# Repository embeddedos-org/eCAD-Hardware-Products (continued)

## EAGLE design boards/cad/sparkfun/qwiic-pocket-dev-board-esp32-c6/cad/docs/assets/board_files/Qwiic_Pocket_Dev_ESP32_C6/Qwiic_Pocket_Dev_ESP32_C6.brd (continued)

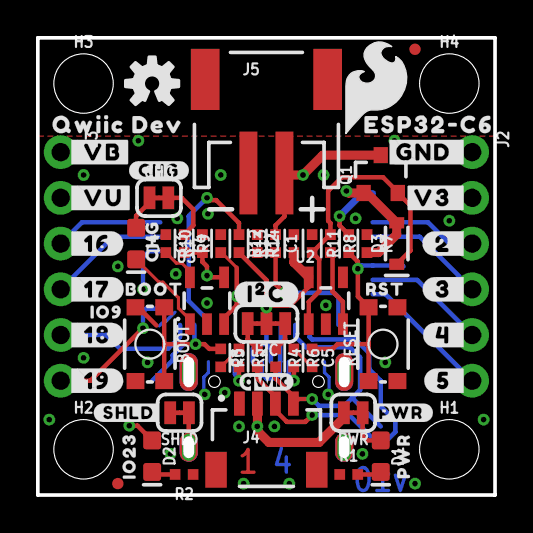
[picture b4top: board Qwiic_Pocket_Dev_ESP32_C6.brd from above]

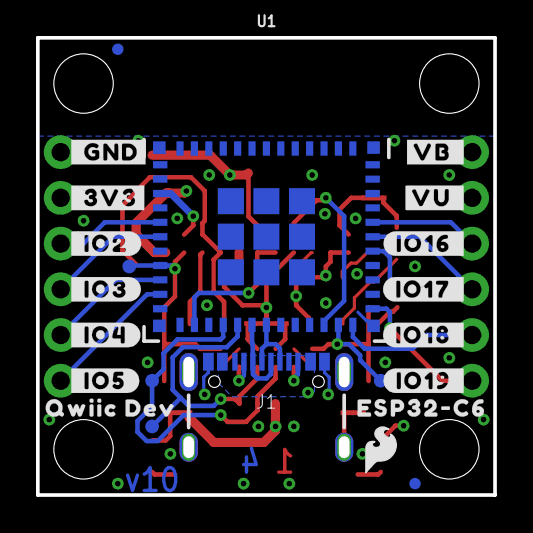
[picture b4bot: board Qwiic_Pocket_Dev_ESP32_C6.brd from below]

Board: 4 copper layers, 25.4 x 25.4 mm, 96 parts (23 on the bottom side), 35 nets.

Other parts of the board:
U$1: #_GND#0
U$2: #_3V3#0
U$3: #V3_#0
U$5: #GND_#0
U$6: SFE_LOGO_FLAME_.2
U$7: #VU_#0
U$8: #_VB#0
U$9, U$25: QWIIC_DEV0
U$10: SFE_LOGO_FLAME_.1
U$11, U$12: ESP32#C633
U$13: #_IO5#0
U$14: #_IO4#0
U$15: #_IO3#0
U$16: #_IO2#0
U$17: #IO16_#0
U$18: #IO17_#0
U$19: #IO18_#0
U$20: #IO19_#0
U$21: #5_#0
U$22: #4_#0
U$23: #I�C#0
U$24: ORDERING_INSTRUCTIONS
U$26: #PWR#0
U$27: #SHLD#0
U$28: IO230
U$30: PWR0
U$31: #CHG#0
U$32: CHG0
U$33: BOOT0
U$34: RST0
U$35: IO90
U$36: #VB_#0
U$37: #_VU#0
U$38: #3_#0
U$39: #2_#0
U$40: #_16#0
U$41: #_17#0
U$42: #_18#0
U$43: #_19#0

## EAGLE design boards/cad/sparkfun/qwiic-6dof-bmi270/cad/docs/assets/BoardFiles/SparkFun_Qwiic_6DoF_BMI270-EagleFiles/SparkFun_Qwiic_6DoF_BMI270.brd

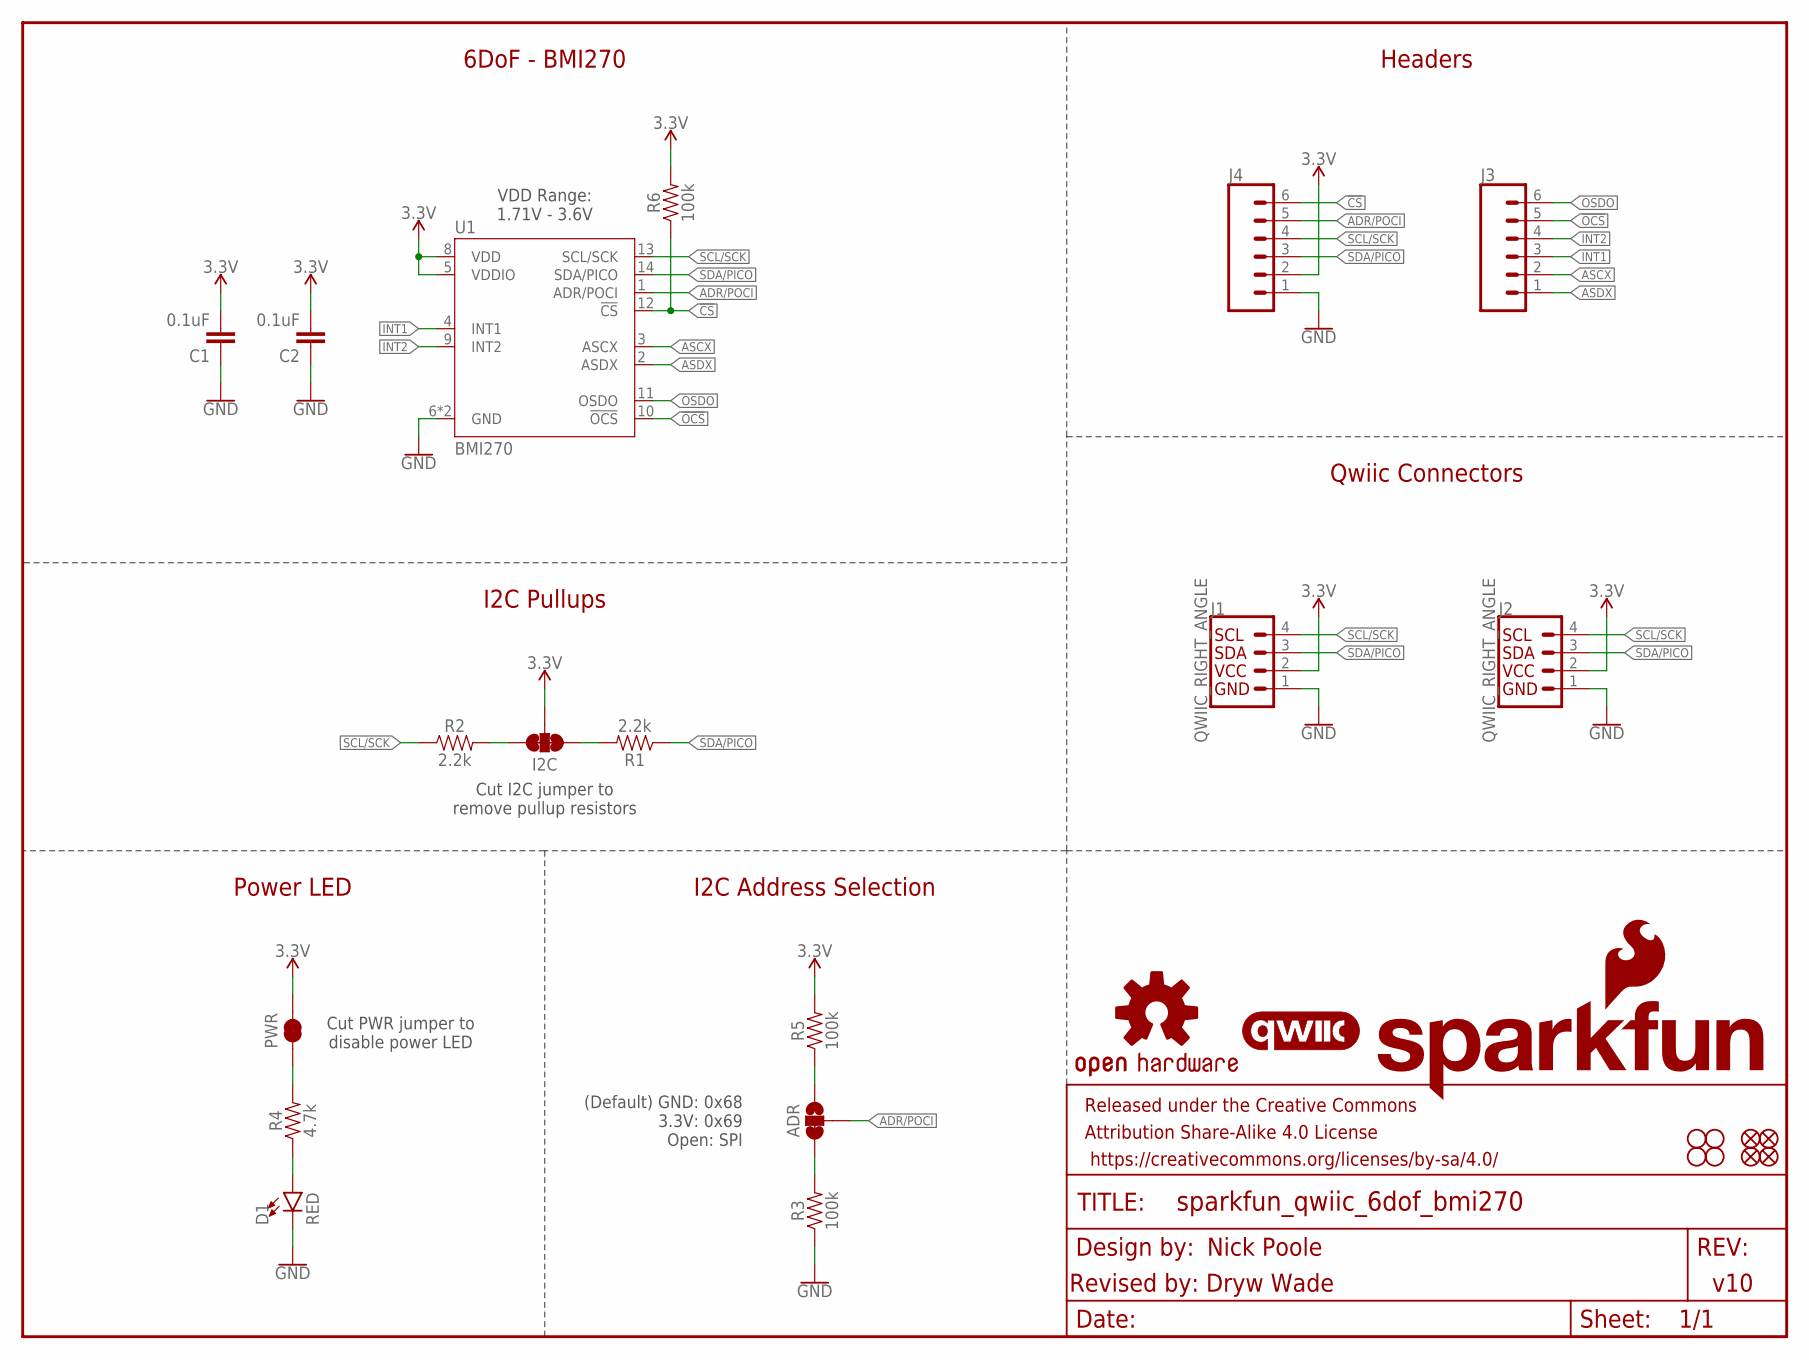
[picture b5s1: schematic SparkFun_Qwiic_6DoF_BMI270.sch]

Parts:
ADR: JUMPER-SMT_3_1-NC_TRACE_SILK; SMT-JUMPER_3_1-NC_TRACE_SILK
C1, C2: 0.1uF; 0603
D1: RED; LED-0603
FD1, FD2, FD3, FD4: FIDUCIAL1X2; FIDUCIAL-1X2
FRAME1: FRAME-LETTER; CREATIVE_COMMONS
H1, H2, H3, H4: STAND-OFF
I2C: JUMPER-SMT_3_2-NC_TRACE_SILK; SMT-JUMPER_3_2-NC_TRACE_SILK
J1, J2: QWIIC_RIGHT_ANGLE; JST04_1MM_RA
J3, J4: CONN_06NO_SILK_NO_POP; 1X06_NO_SILK
LOGO1: SFE_LOGO_NAME_FLAME.1_INCH; SFE_LOGO_NAME_FLAME_.1
LOGO2: QWIIC_LOGO_5MM; QWIIC_5MM
LOGO3: OSHW-LOGOS; OSHW-LOGO-S
PWR: JUMPER-SMT_2_NC_TRACE_SILK; SMT-JUMPER_2_NC_TRACE_SILK
R1, R2: 2.2k; 0603
R3, R5, R6: 100k; 0603
R4: 4.7k; 0603
U1: BMI270

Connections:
3.3V: C1.2, C2.2, I2C.2, J1.2, J2.2, J4.2, PWR.2, R5.2, R6.2, U1.5 (VDDIO), U1.8 (VDD)
!CS!: J4.6, R6.1, U1.12 (!CS!)
!OCS!: J3.5, U1.10 (!OCS!)
ADR/POCI: ADR.2, J4.5, U1.1 (ADR/POCI)
ASCX: J3.2, U1.3 (ASCX)
ASDX: J3.1, U1.2 (ASDX)
GND: C1.1, C2.1, D1.C, J1.1, J2.1, J4.1, R3.1, U1.6 (GND), U1.7 (GND)
INT1: J3.3, U1.4 (INT1)
INT2: J3.4, U1.9 (INT2)
unnamed: I2C.1, R1.2
unnamed: I2C.3, R2.2
unnamed: PWR.1, R4.2
unnamed: D1.A, R4.1
unnamed: ADR.1, R5.1
unnamed: ADR.3, R3.2
OSDO: J3.6, U1.11 (OSDO)
SCL/SCK: J1.4, J2.4, J4.4, R2.1, U1.13 (SCL/SCK)
SDA/PICO: J1.3, J2.3, J4.3, R1.1, U1.14 (SDA/PICO)

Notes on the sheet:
(Default) GND: 0x68 3.3V: 0x69 Open: SPI
Cut PWR jumper to disable power LED
Power LED
Headers
Qwiic Connectors
Nick Poole
Revised by: Dryw Wade
v10
6DoF - BMI270
Cut I2C jumper to remove pullup resistors
VDD Range: 1.71V - 3.6V
I2C Address Selection
I2C Pullups

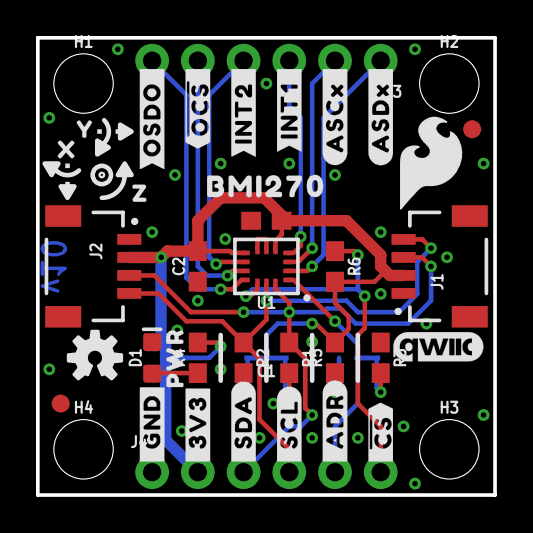
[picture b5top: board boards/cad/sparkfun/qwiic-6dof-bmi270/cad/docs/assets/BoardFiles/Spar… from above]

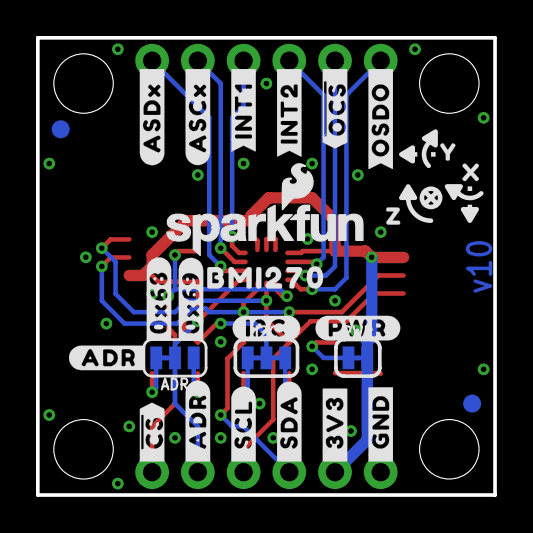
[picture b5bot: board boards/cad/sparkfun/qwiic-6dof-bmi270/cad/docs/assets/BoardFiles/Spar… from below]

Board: 2 copper layers, 25.4 x 25.4 mm, 69 parts (27 on the bottom side), 18 nets.

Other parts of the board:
U$1: #I2C#0
U$2, U$14: #_SDA#0
U$3: SFE_LOGO_FLAME_.2
U$4: #PWR#0
U$5: #ADR#0
U$6: #0X68#0
U$7, U$13: #_3V3#0
U$8, U$17: #_#CS##0
U$9, U$16: #_ADR#0
U$10, U$15: #_SCL#0
U$11, U$27: #ASDX_#0
U$12, U$19: #_GND#0
U$18: #0X69#0
U$20, U$21: BMI2700
U$22, U$28: #ASCX_#0
U$23, U$29: #INT1_#0
U$24, U$30: #INT2_#0
U$25, U$31: ##OCS#_#0
U$26, U$32: #OSDO_#0
U$33: ORDERING_INSTRUCTIONS
U$34: PWR0
U$79, U$88: X0
U$80, U$89: Y0
U$81, U$90: Z0

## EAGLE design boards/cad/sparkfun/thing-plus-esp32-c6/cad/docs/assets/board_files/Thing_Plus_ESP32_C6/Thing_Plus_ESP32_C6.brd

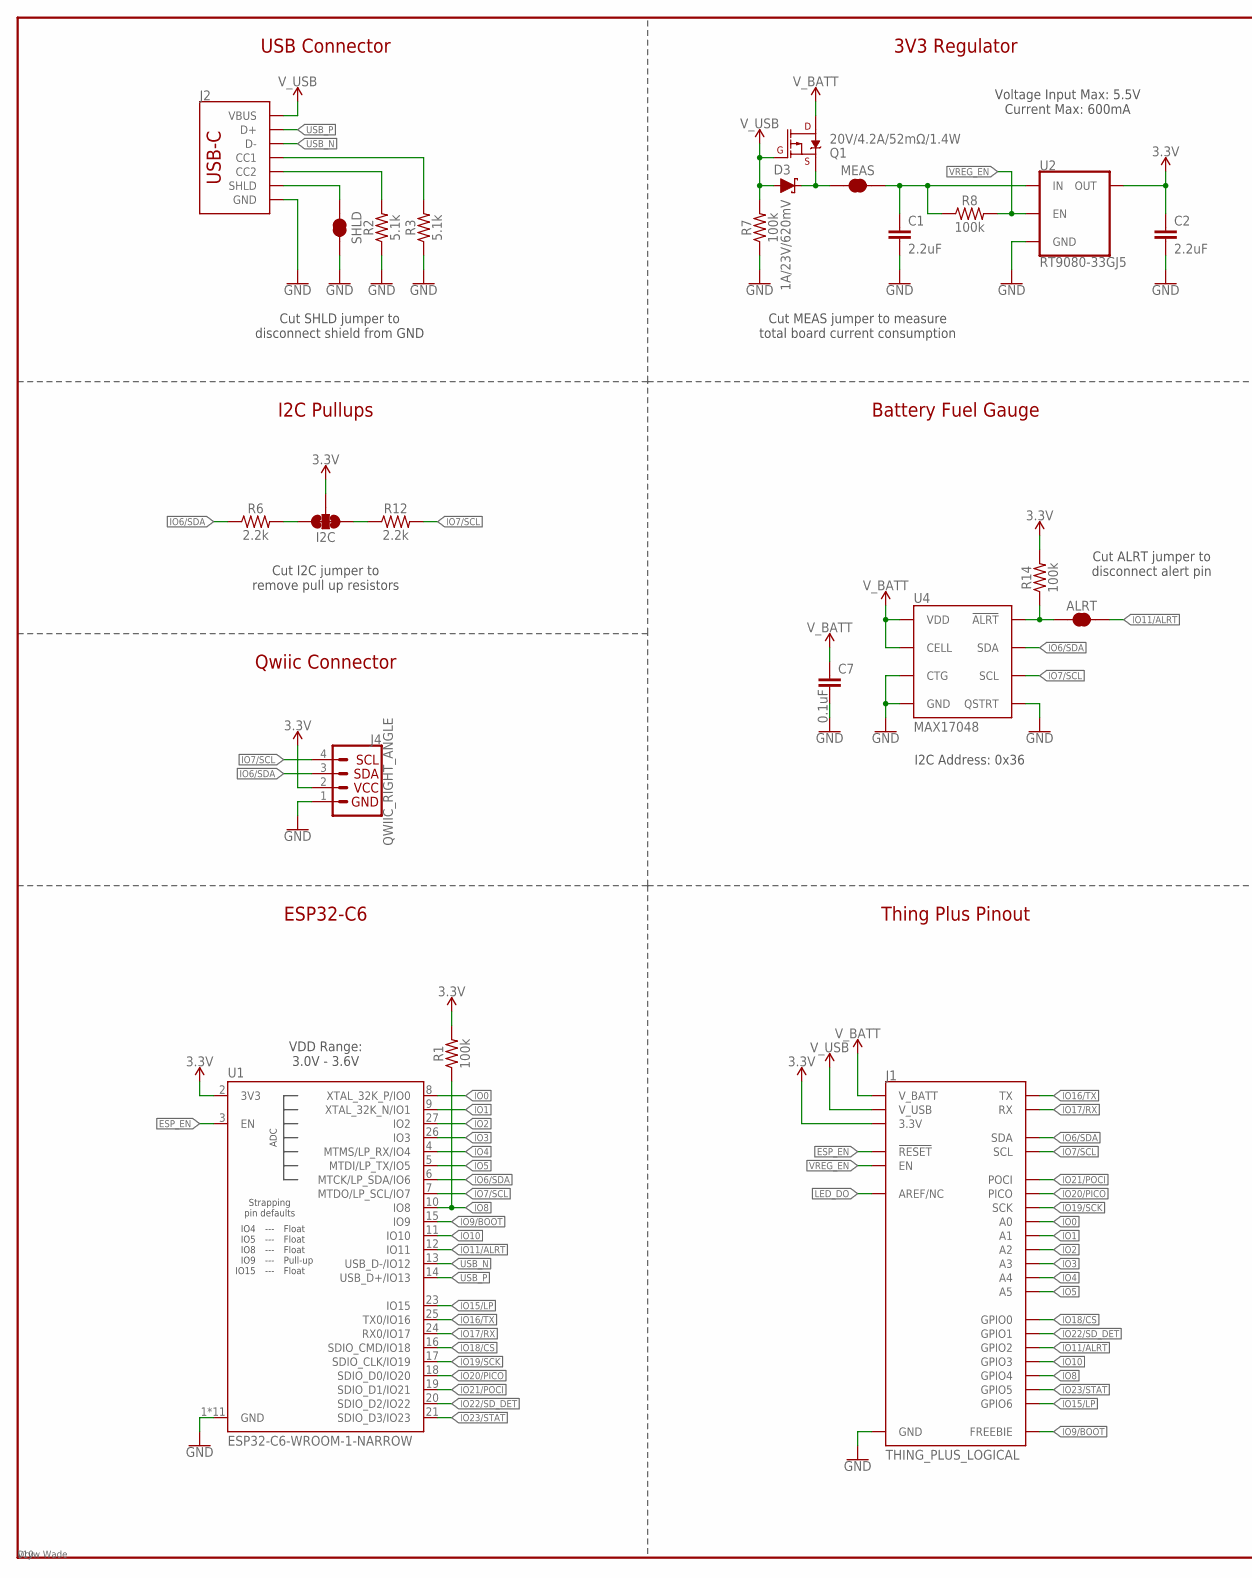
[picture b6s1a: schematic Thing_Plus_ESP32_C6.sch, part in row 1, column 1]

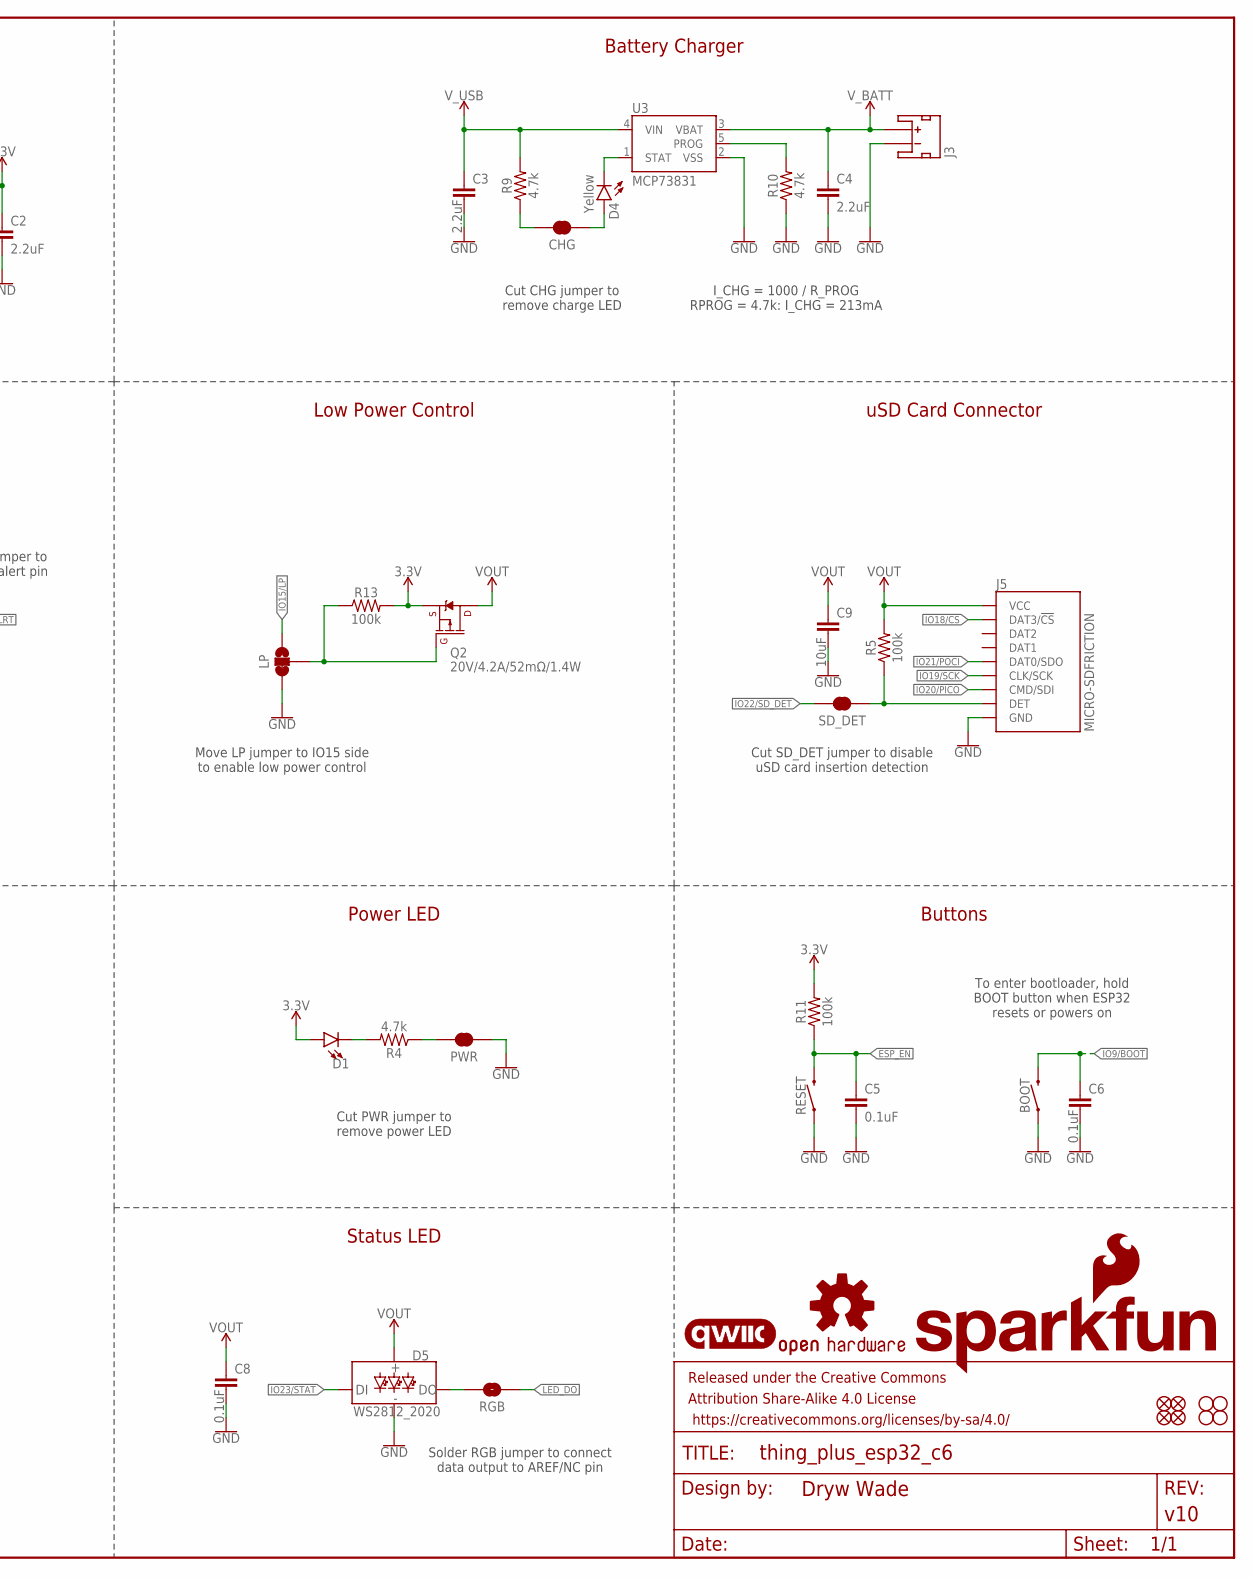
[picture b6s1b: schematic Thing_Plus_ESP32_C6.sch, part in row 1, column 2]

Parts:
ALRT: JUMPER-SMT_2_NC_TRACE_SILK; SMT-JUMPER_2_NC_TRACE_SILK
BOOT: MOMENTARY-SWITCH-SPST-SMD-4.6X2.8MM; TACTILE_SWITCH_SMD_4.6X2.8MM
C1, C2, C3, C4: 2.2uF; 0603
C5, C6, C7, C8: 0.1uF; 0603
C9: 10uF; 0603
CHG: JUMPER-SMT_2_NC_TRACE_SILK; SMT-JUMPER_2_NC_TRACE_SILK
D1: LED-RED_0603-KB; LED-0603
D3: 1A/23V/620mV; SOD-323
D4: Yellow; LED-0603
D5: WS2812_2020; WS2812-2020
FD1, FD2, FD3, FD4: FIDUCIALUFIDUCIAL; FIDUCIAL-MICRO
FRAME1: FRAME-LEDGER; CREATIVE_COMMONS
H1, H2, H3, H4: STAND-OFF
I2C: JUMPER-SMT_3_2-NC_TRACE_SILK; SMT-JUMPER_3_2-NC_TRACE_SILK
J1: THING_PLUS_LOGICAL; THING_PLUS
J2: USB_C_4-LAYER_PADS; USB-C-16P_4LAYER-PADS
J3: JST_2MM_MALE; JST-2-SMD
J4: QWIIC_RIGHT_ANGLE; JST04_1MM_RA
J5: MICRO-SDFRICTION; MICROSD_TINY
LOGO1: SFE_LOGO_NAME_FLAME.1_INCH; SFE_LOGO_NAME_FLAME_.1
LOGO2: QWIIC_LOGO_4MM; QWIIC_4MM
LOGO3: OSHW-LOGOM; OSHW-LOGO-M
LP: JUMPER-SMT_3_1-NC_TRACE_SILK; SMT-JUMPER_3_1-NC_TRACE_SILK
MEAS: JUMPER-COMBO_2_NC_TRACE; COMBO-JUMPER_2_NC_TRACE
PWR: JUMPER-SMT_2_NC_TRACE_SILK; SMT-JUMPER_2_NC_TRACE_SILK
Q1, Q2: 20V/4.2A/52mΩ/1.4W; SOT23-3
R1, R5, R7, R8, R11, R13, R14: 100k; 0603
R2, R3: 5.1k; 0603
R4, R9, R10: 4.7k; 0603
R6, R12: 2.2k; 0603
RESET: MOMENTARY-SWITCH-SPST-SMD-4.6X2.8MM; TACTILE_SWITCH_SMD_4.6X2.8MM
RGB: JUMPER-SMT_2_NO_SILK; SMT-JUMPER_2_NO_SILK
SD_DET: JUMPER-SMT_2_NC_TRACE_SILK; SMT-JUMPER_2_NC_TRACE_SILK
SHLD: JUMPER-SMT_2_NC_TRACE_SILK; SMT-JUMPER_2_NC_TRACE_SILK
U1: ESP32-C6-WROOM-1-NARROW
U2: RT9080-33GJ5; SOT23-5
U3: MCP73831; SOT23-5
U4: MAX17048; DFN-8

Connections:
3.3V: C2.1, D1.A, I2C.2, J1.27 (3.3V), J4.2, Q2.2 (S), R1.2, R11.2, R13.2, R14.2, U1.2 (3V3), U2.5 (OUT)
ESP_EN: C5.1, J1.28 (!RESET), R11.1, RESET.3 (2), RESET.4 (2), U1.3 (EN)
GND: BOOT.1, BOOT.2 (1), C1.2, C2.2, C3.2, C4.2, C5.2, C6.2, C7.2, C8.2, C9.2, D5.GND, J1.25 (GND), J2.GND, J2.GND2 (GND), J3.1 (-), J4.1, J5.6 (GND), J5.GND1 (GND), J5.GND2 (GND), J5.GND3 (GND), J5.GND4 (GND), J5.GND5 (GND), J5.GND6 (GND), LP.3, PWR.1, R2.1, R3.1, R7.1, R10.1, RESET.1, RESET.2 (1), SHLD.2, U1.1 (GND), U1.28 (GND), U1.29 (GND), U1.30 (GND), U1.31 (GND), U1.32 (GND), U1.33 (GND), U1.34 (GND), U1.35 (GND), U1.36 (GND), U1.37 (GND), U2.2 (GND), U3.2 (VSS), U4.1 (CTG), U4.4 (GND), U4.6 (QSTRT), U4.9 (GND)
IO0: J1.24 (A0), U1.8 (XTAL_32K_P/IO0)
IO1: J1.23 (A1), U1.9 (XTAL_32K_N/IO1)
IO2: J1.22 (A2), U1.27 (IO2)
IO3: J1.21 (A3), U1.26 (IO3)
IO4: J1.20 (A4), U1.4 (MTMS/LP_RX/IO4)
IO5: J1.19 (A5), U1.5 (MTDI/LP_TX/IO5)
IO6/SDA: J1.1 (SDA), J4.3, R6.1, U1.6 (MTCK/LP_SDA/IO6), U4.8 (SDA)
IO7/SCL: J1.2 (SCL), J4.4, R12.2, U1.7 (MTDO/LP_SCL/IO7), U4.7 (SCL)
IO8: J1.5 (GPIO4), R1.1, U1.10 (IO8)
IO9/BOOT: BOOT.3 (2), BOOT.4 (2), C6.1, J1.13 (FREEBIE), U1.15 (IO9)
IO10: J1.6 (GPIO3), U1.11 (IO10)
IO11/!ALRT!: ALRT.2, J1.7 (GPIO2), U1.12 (IO11)
IO15/LP: J1.3 (GPIO6), LP.1, U1.23 (IO15)
IO16/TX: J1.14 (TX), U1.25 (TX0/IO16)
IO17/RX: J1.15 (RX), U1.24 (RX0/IO17)
IO18/!CS!: J1.9 (GPIO0), J5.2 (DAT3/!CS!), U1.16 (SDIO_CMD/IO18)
IO19/SCK: J1.18 (SCK), J5.5 (CLK/SCK), U1.17 (SDIO_CLK/IO19)
IO20/PICO: J1.17 (PICO), J5.3 (CMD/SDI), U1.18 (SDIO_D0/IO20)
IO21/POCI: J1.16 (POCI), J5.7 (DAT0/SDO), U1.19 (SDIO_D1/IO21)
IO22/!SD_DET!: J1.8 (GPIO1), SD_DET.2, U1.20 (SDIO_D2/IO22)
IO23/STAT: D5.DI, J1.4 (GPIO5), U1.21 (SDIO_D3/IO23)
LED_DO: J1.26 (AREF/NC), RGB.1
unnamed: D1.C, R4.2
unnamed: PWR.2, R4.1
unnamed: J5.9 (DET), R5.1, SD_DET.1
unnamed: D3.C, MEAS.1, MEAS.3 (1), Q1.2 (S)
unnamed: I2C.3, R6.2
unnamed: I2C.1, R12.1
unnamed: J2.B5 (CC2), R2.2
unnamed: J2.A5 (CC1), R3.2
unnamed: C1.1, MEAS.2, MEAS.4 (2), R8.1, U2.1 (IN)
unnamed: D4.C, U3.1 (STAT)
unnamed: CHG.1, D4.A
unnamed: CHG.2, R9.1
unnamed: R10.2, U3.5 (PROG)
unnamed: D5.DO, RGB.2
unnamed: LP.2, Q2.1 (G), R13.1
unnamed: ALRT.1, R14.1, U4.5 (!ALRT)
SHLD: J2.SHLD1 (SHLD), J2.SHLD2 (SHLD), J2.SHLD3 (SHLD), J2.SHLD4 (SHLD), SHLD.1
USB_N: J2.A7 (D-), J2.B7 (D-), U1.13 (USB_D-/IO12)
USB_P: J2.A6 (D+), J2.B6 (D+), U1.14 (USB_D+/IO13)
VOUT: C8.1, C9.1, D5.VCC, J5.4 (VCC), Q2.3 (D), R5.2
VREG_EN: J1.11 (EN), R8.2, U2.3 (EN)
V_BATT: C4.1, C7.1, J1.12 (V_BATT), J3.2 (+), Q1.3 (D), U3.3 (VBAT), U4.2 (CELL), U4.3 (VDD)
V_USB: C3.1, D3.A, J1.10 (V_USB), J2.VBUS1 (VBUS), J2.VBUS2 (VBUS), Q1.1 (G), R7.2, R9.2, U3.4 (VIN)

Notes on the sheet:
ESP32-C6
VDD Range: 3.0V - 3.6V
Buttons
3V3 Regulator
USB Connector
Battery Charger
Cut CHG jumper to remove charge LED
I_CHG = 1000 / R_PROG RPROG = 4.7k: I_CHG = 213mA
Power LED
Cut PWR jumper to remove power LED
Thing Plus Pinout
I2C Pullups
Cut I2C jumper to remove pull up resistors
I2C Address: 0x36
Qwiic Connector
Battery Fuel Gauge
uSD Card Connector
Cut SHLD jumper to disconnect shield from GND
Cut MEAS jumper to measure total board current consumption
Voltage Input Max: 5.5V Current Max: 600mA
Cut SD_DET jumper to disable uSD card insertion detection
Solder RGB jumper to connect data output to AREF/NC pin
Move LP jumper to IO15 side to enable low power control
To enter bootloader, hold BOOT button when ESP32 resets or powers on
Cut ALRT jumper to disconnect alert pin
Low Power Control
Status LED

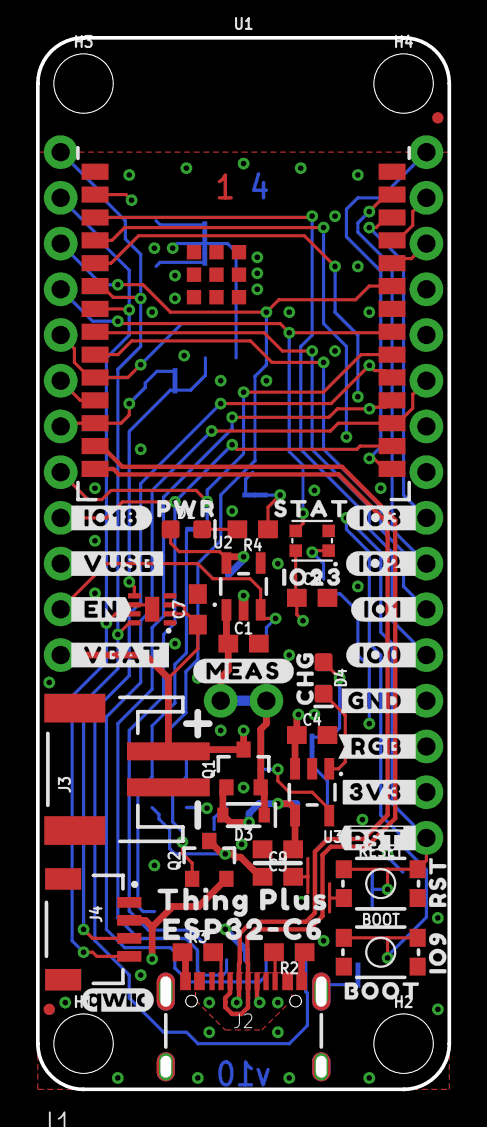
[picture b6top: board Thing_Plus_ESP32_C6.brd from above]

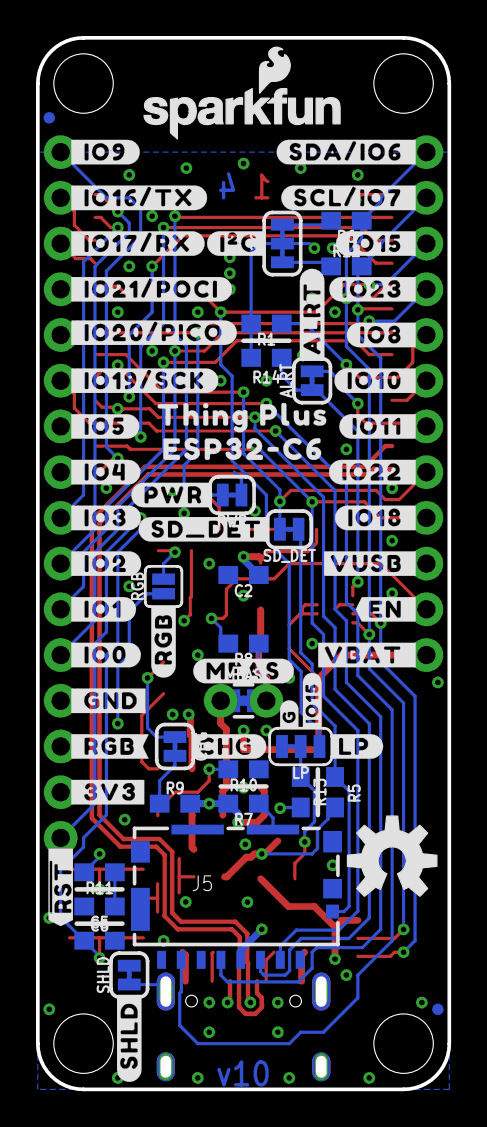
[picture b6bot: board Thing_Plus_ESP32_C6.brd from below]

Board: 4 copper layers, 22.9 x 58.4 mm, 125 parts (69 on the bottom side), 48 nets.

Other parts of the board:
U$1: #SHLD#0
U$2: #I�C#0
U$3: #_IO18#0
U$4: #_VUSB#0
U$5: #_VBAT#0
U$6: #_EN#0
U$7: #IO3_#0
U$8: #IO2_#0
U$9: #IO1_#0
U$10: #IO0_#0
U$11: #GND_#0
U$12: #3V3_#0
U$13, U$37: ##RST#_#0
U$14: #SDA#IO6_#0
U$15: #SCL#IO7_#0
U$16: #_IO21#POCI#0
U$17: #LP#0
U$18: #IO8_#0
U$19: #IO10_#0
U$20: #IO11_#0
U$21: #_IO19#SCK#0
U$22: #IO18_#0
U$23: #_IO9#0
U$24: #_IO16#TX#0
U$25: #_IO17#RX#0
U$26: #_IO20#PICO#0
U$27: #IO15#0
U$28: #ALRT#0
U$29: #_IO5#0
U$30: #_IO4#0
U$31: #_IO3#0
U$32: #_IO2#0
U$33: #_IO1#0
U$34: #_IO0#0
U$35: #_GND#0
U$36: #_3V3#0
U$38: #VUSB_#0
U$39: #VBAT_#0
U$40: #EN_#0
U$41: #SD_DET#0
U$42: BOOT0
U$43: RST0
U$44: IO90
U$45, U$47: THING_PLUS0
U$46, U$48: ESP32#C60
U$49, U$50: #MEAS#0
U$51: #CHG#0
U$52: #PWR#0
U$53: PWR0
U$54: CHG0
U$55: STAT0
U$56: #RGB#0
U$57: ORDERING_INSTRUCTIONS
U$58: #RGB_#0
U$59: #_RGB#0
U$62: IO230
U$63: #G#0
U$64: #IO23_#0
U$65: #IO15_#0
U$66: #IO22_#0

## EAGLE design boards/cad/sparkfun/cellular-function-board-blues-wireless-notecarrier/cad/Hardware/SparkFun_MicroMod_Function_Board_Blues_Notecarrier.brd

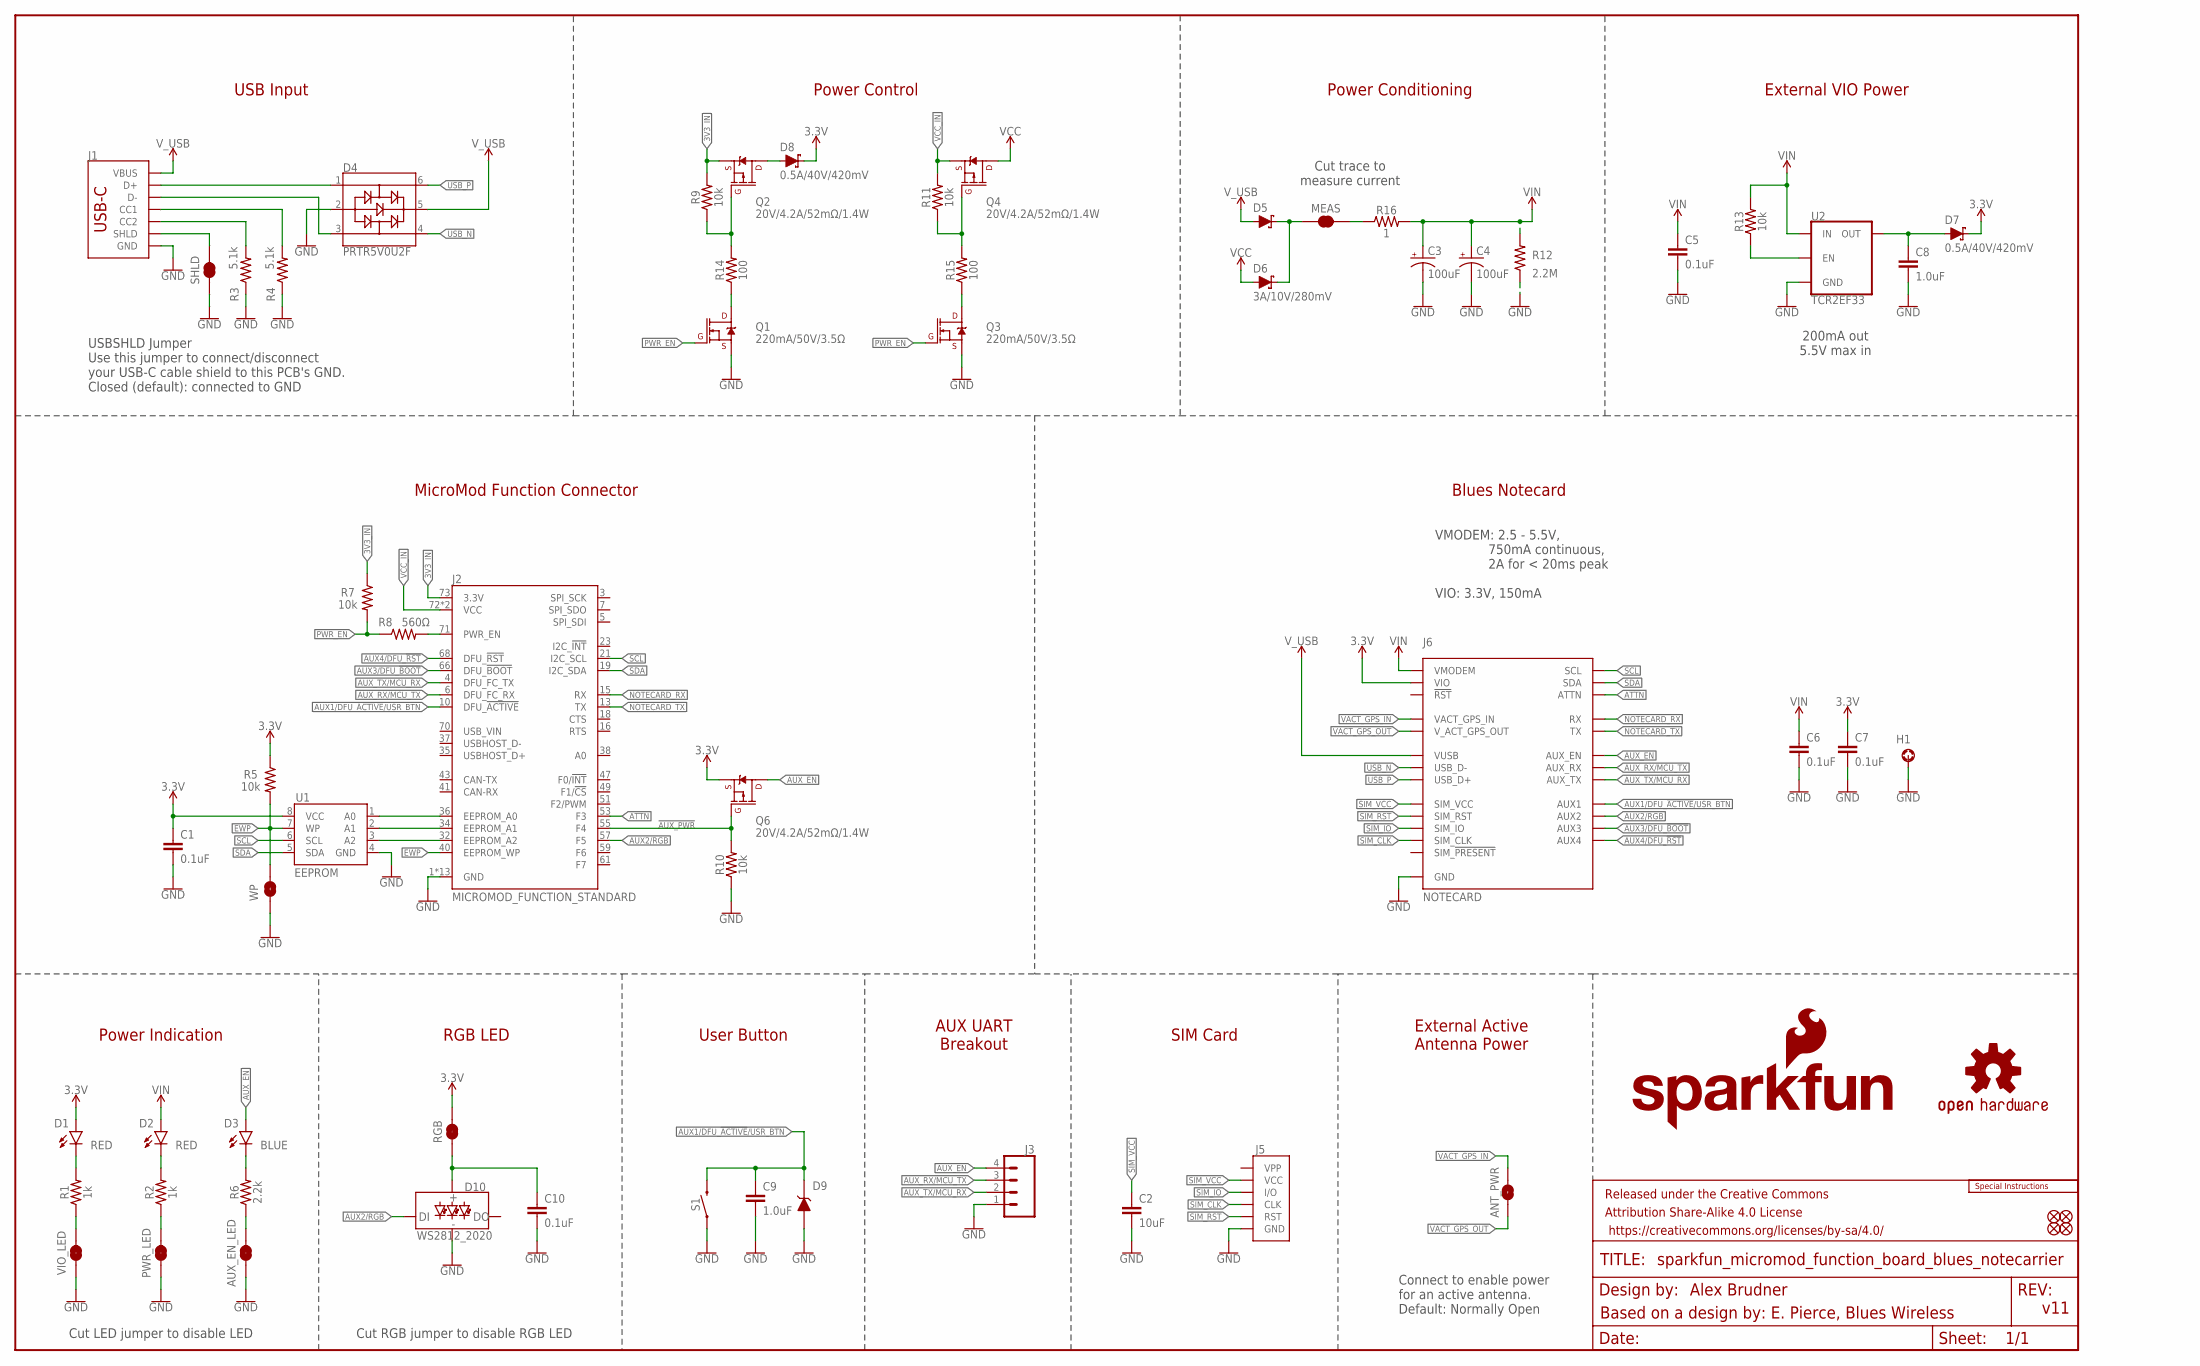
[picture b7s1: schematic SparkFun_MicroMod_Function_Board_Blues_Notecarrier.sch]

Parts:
ANT_PWR: JUMPER-SMT_2_NO_SILK; SMT-JUMPER_2_NO_SILK
AUX_EN_LED: JUMPER-SMT_2_NC_TRACE_SILK; SMT-JUMPER_2_NC_TRACE_SILK
C1, C5, C6, C7, C10: 0.1uF; 0402-TIGHT
C2: 10uF; 0805
C3, C4: 100uF; PANASONIC_D
C8, C9: 1.0uF; 0402-TIGHT
D1, D2: RED; LED-0603
D3: BLUE; LED-0603
D4: PRTR5V0U2F; SOT886
D5, D6: 3A/10V/280mV; SOD-323
D7, D8: 0.5A/40V/420mV; SOD-323
D9: SMBJP6KE-DNP; DO-214AA
D10: WS2812_2020; WS2812-2020
FD1, FD2, FD3, FD4: FIDUCIALUFIDUCIAL; FIDUCIAL-MICRO
FRAME1: FRAME-LEDGER; CREATIVE_COMMONS
H1: STAND-OFF-REFLOW-M2.5_2.5MM_TALL; STAND-OFF-REFLOW-M2.5
J1: USB_C_2-LAYER_PADS; USB-C-16P-2LAYER-PADS
J2: MICROMOD_FUNCTION_STANDARD; M.2-CARD-E-22_FUNCTION_STANDARD
J3: CONN_041X04_NO_SILK_NO_POP; 1X04_NO_SILK
J5: SIMHOLDER-NANOSIM-MOLEX; NANO_SIM_MOLEX_104224-0820
J6: NOTECARD; M.2-CONNECTOR-E
LOGO1: SFE_LOGO_NAME_FLAME.1_INCH; SFE_LOGO_NAME_FLAME_.1
LOGO2: SPECIAL_INSTRUCTIONS-ORDERING; ORDERING_INSTRUCTIONS
LOGO3: OSHW-LOGOMINI; OSHW-LOGO-MINI
MEAS: JUMPER-COMBO_2_NC_TRACE; COMBO-JUMPER_2_NC_TRACE
PWR_LED: JUMPER-SMT_2_NC_TRACE_SILK; SMT-JUMPER_2_NC_TRACE_SILK
Q1, Q3: 220mA/50V/3.5Ω; SOT23-3
Q2, Q4, Q6: 20V/4.2A/52mΩ/1.4W; SOT23-3
R1, R2: 1k; 0402-TIGHT
R3, R4: 5.1k; 0402-TIGHT
R5, R7, R9, R10, R11, R13: 10k; 0402-TIGHT
R6: 2.2k; 0402-TIGHT
R8: 560Ω; 0402-TIGHT
R12: 2.2M; 0402-TIGHT
R14, R15: 100; 0402-TIGHT
R16: 1; 0603
RGB: JUMPER-SMT_2_NC_TRACE_SILK; SMT-JUMPER_2_NC_TRACE_SILK
S1: MOMENTARY-SWITCH-SPST-SMD-4.6X2.8MM; TACTILE_SWITCH_SMD_4.6X2.8MM
SHLD: JUMPER-SMT_2_NC_TRACE_SILK; SMT-JUMPER_2_NC_TRACE_SILK
U1: EEPROM; SO08
U2: TCR2EF33; SOT23-5
VIO_LED: JUMPER-SMT_2_NC_TRACE_SILK; SMT-JUMPER_2_NC_TRACE_SILK
WP: JUMPER-SMT_2_NO_SILK; SMT-JUMPER_2_NO_SILK

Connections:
3.3V: C1.1, C7.1, D1.A, D7.C, D8.C, J6.2 (VIO), J6.4 (VIO), Q6.2 (S), R5.1, RGB.2, U1.8 (VCC)
3V3_IN: J2.73 (3.3V), Q2.2 (S), R7.1, R9.2
!AUX_PWR!: J2.55 (F4), Q6.1 (G), R10.2
A0: J2.36 (EEPROM_A0), U1.1 (A0)
A1: J2.34 (EEPROM_A1), U1.2 (A1)
A2: J2.32 (EEPROM_A2), U1.3 (A2)
ATTN: J2.53 (F3), J6.54 (ATTN)
AUX1/DFU_!ACTIVE!/USR_BTN: C9.1, D9.C, J2.10 (DFU_!ACTIVE!), J6.46 (AUX1), S1.3 (2), S1.4 (2)
AUX2/RGB: D10.DI, J2.57 (F5), J6.48 (AUX2)
AUX3/DFU_!BOOT!: J2.66 (DFU_!BOOT!), J6.50 (AUX3)
AUX4/DFU_!RST!: J2.68 (DFU_!RST!), J6.52 (AUX4)
AUX_EN: D3.A, J3.4, J6.56 (AUX_EN), Q6.3 (D)
AUX_RX/MCU_TX: J2.6 (DFU_FC_RX), J3.3, J6.58 (AUX_RX)
AUX_TX/MCU_RX: J2.4 (DFU_FC_TX), J3.2, J6.60 (AUX_TX)
EWP: J2.40 (EEPROM_WP), R5.2, U1.7 (WP), WP.2
GND: AUX_EN_LED.1, C1.2, C2.2, C3.-, C4.-, C5.2, C6.2, C7.2, C8.2, C9.2, C10.2, D4.2, D9.A, D10.GND, H1.1, J1.GND, J1.GND2 (GND), J2.1 (GND), J2.2 (GND), J2.8 (GND), J2.33 (GND), J2.39 (GND), J2.45 (GND), J2.75 (GND), J2.GND1 (GND), J2.GND2 (GND), J2.GND3 (GND), J2.GND4 (GND), J2.GND5 (GND), J2.GND6 (GND), J3.1, J5.G1 (GND), J5.G2 (GND), J5.G3 (GND), J5.G4 (GND), J5.S4 (GND), J6.3 (GND), J6.5 (GND), J6.6 (GND), J6.11 (GND), J6.18 (GND), J6.33 (GND), J6.39 (GND), J6.45 (GND), J6.51 (GND), J6.57 (GND), J6.71 (GND), J6.73 (GND), PWR_LED.1, Q1.2 (S), Q3.2 (S), R3.1, R4.1, R10.1, R12.1, S1.1, S1.2 (1), SHLD.1, U1.4 (GND), U2.2 (GND), VIO_LED.1, WP.1
unnamed: J2.71 (PWR_EN), R8.2
unnamed: Q2.1 (G), R9.1, R14.2
unnamed: Q4.1 (G), R11.1, R15.2
unnamed: D1.C, R1.2
unnamed: R13.1, U2.3 (EN)
unnamed: D2.C, R2.2
unnamed: D8.A, Q2.3 (D)
unnamed: J1.B5 (CC2), R3.2
unnamed: J1.A5 (CC1), R4.2
unnamed: C8.1, D7.A, U2.5 (OUT)
unnamed: PWR_LED.2, R2.1
unnamed: R1.1, VIO_LED.2
unnamed: D3.C, R6.2
unnamed: AUX_EN_LED.2, R6.1
unnamed: Q1.3 (D), R14.1
unnamed: Q3.3 (D), R15.1
unnamed: MEAS.2, MEAS.4 (2), R16.1
unnamed: C10.1, D10.VCC, RGB.1
unnamed: D5.C, D6.C, MEAS.1, MEAS.3 (1)
NOTECARD_RX: J2.15 (RX), J6.62 (RX)
NOTECARD_TX: J2.13 (TX), J6.64 (TX)
PWR_EN: Q1.1 (G), Q3.1 (G), R7.2, R8.1
SCL: J2.21 (I2C_SCL), J6.40 (SCL), U1.6 (SCL)
SDA: J2.19 (I2C_SDA), J6.42 (SDA), U1.5 (SDA)
SHLD: J1.SHLD1 (SHLD), J1.SHLD2 (SHLD), J1.SHLD3 (SHLD), J1.SHLD4 (SHLD), SHLD.2
SIM_CLK: J5.S3 (CLK), J6.14 (SIM_CLK)
SIM_IO: J5.S6 (I/O), J6.12 (SIM_IO)
SIM_RST: J5.S2 (RST), J6.10 (SIM_RST)
SIM_VCC: C2.1, J5.S1 (VCC), J6.8 (SIM_VCC)
USB_IN_N: D4.3, J1.A7 (D-), J1.B7 (D-)
USB_IN_P: D4.1, J1.A6 (D+), J1.B6 (D+)
USB_N: D4.4, J6.9 (USB_D-)
USB_P: D4.6, J6.7 (USB_D+)
VACT_GPS_IN: ANT_PWR.2, J6.22 (VACT_GPS_IN)
VACT_GPS_OUT: ANT_PWR.1, J6.20 (V_ACT_GPS_OUT)
VCC: D6.A, Q4.3 (D)
VCC_IN: J2.72 (VCC), J2.74 (VCC), Q4.2 (S), R11.2
VIN: C3.+, C4.+, C5.1, C6.1, D2.A, J6.70 (VMODEM), J6.72 (VMODEM), J6.74 (VMODEM), R12.2, R13.2, R16.2, U2.1 (IN)
V_USB: D4.5, D5.A, J1.VBUS1 (VBUS), J1.VBUS2 (VBUS), J6.13 (VUSB)

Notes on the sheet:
Alex Brudner
Based on a design by: E. Pierce, Blues Wireless
v11
MicroMod Function Connector
Power Control
USB Input
Power Conditioning
Blues Notecard
Power Indication
User Button
AUX UART Breakout
SIM Card
External Active Antenna Power
External VIO Power
200mA out 5.5V max in
VMODEM: 2.5 - 5.5V, 750mA continuous, 2A for < 20ms peak VIO: 3.3V, 150mA
USBSHLD Jumper Use this jumper to connect/disconnect your USB-C cable shield to this PCB's GND. Closed (default): connected to GND
Cut LED jumper to disable LED
Cut trace to measure current
Connect to enable power for an active antenna. Default: Normally Open
RGB LED
Cut RGB jumper to disable RGB LED

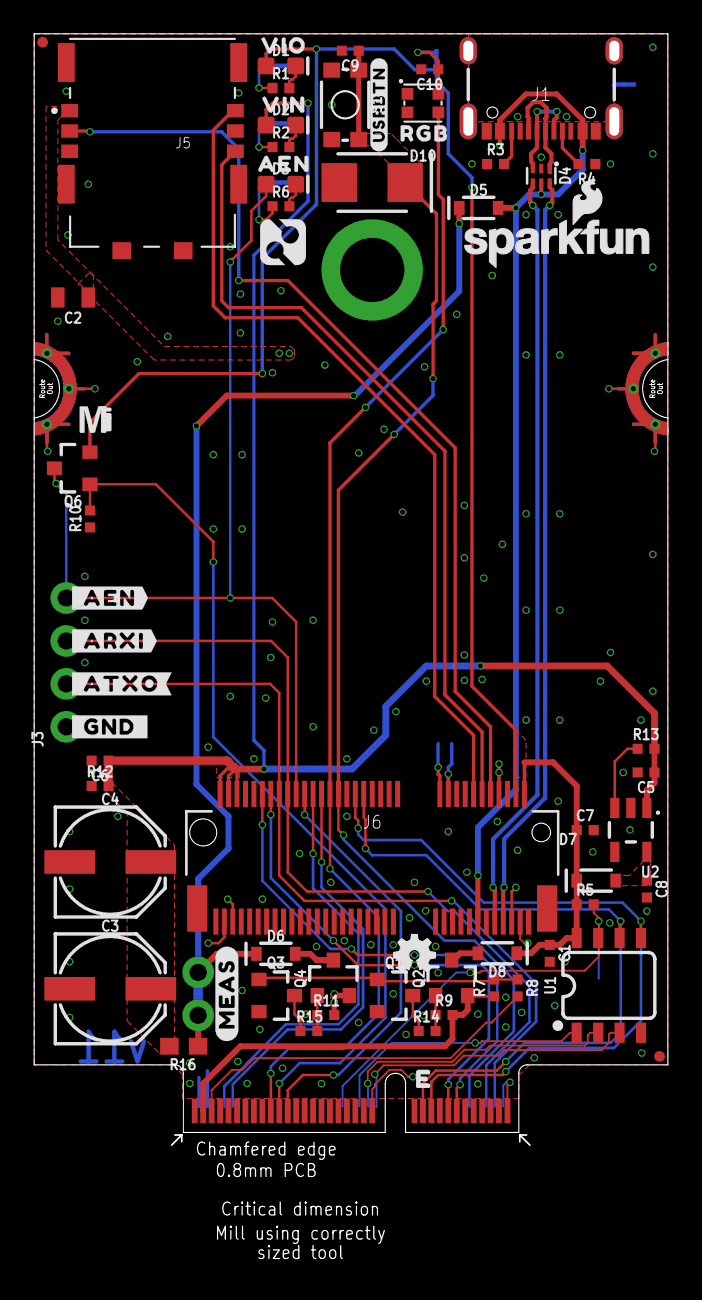
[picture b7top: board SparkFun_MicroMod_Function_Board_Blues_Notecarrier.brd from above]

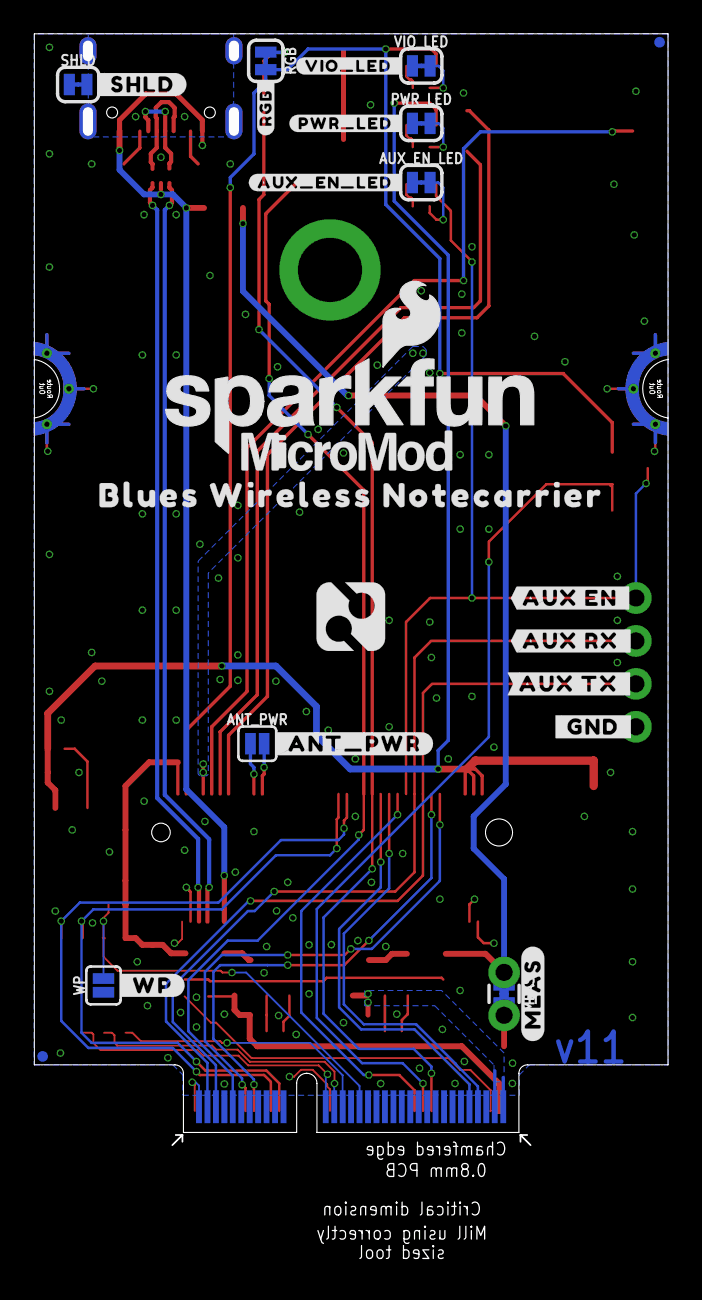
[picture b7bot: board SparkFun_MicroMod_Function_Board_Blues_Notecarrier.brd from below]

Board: 2 copper layers, 37.5 x 65.8 mm, 95 parts (26 on the bottom side), 55 nets.

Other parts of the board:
U$1: AEN1
U$2: VIN3
U$3: VIO4
U$4: #VIO_LED_#21
U$5: #_ARXI#0
U$6: SFE_LOGO_FLAME_STOP_.1
U$7: #_GND_#0
U$8: #_WP#2
U$9: BLUES_WIRELESS_NOTECARRIER0
U$10: NOTEHUB_BLUES#SVG7
U$11: #_ATXO#0
U$12: #AUX_TX_#0
U$13: #_AEN#0
U$14: SFE_LOGO_NAME_FLAME_.2
U$15: #AUX_RX_#0
U$16, U$17: #MEAS#4
U$18: #_ANT_PWR#5
U$19: #AUX_EN_LED_#20
U$20: #_SHLD#23
U$21: #PWR_LED_#17
U$22: #_GND_#24
U$23: NOTEHUB_BLUES#SVG5
U$24: #RGB_#0
U$25: #USRBTN#0
U$26: RGB0
U$29: MICROMOD_MI_LOGO_.35
U$30: #AUX_EN_#0
U$31: MICROMOD_LOGO_.5
